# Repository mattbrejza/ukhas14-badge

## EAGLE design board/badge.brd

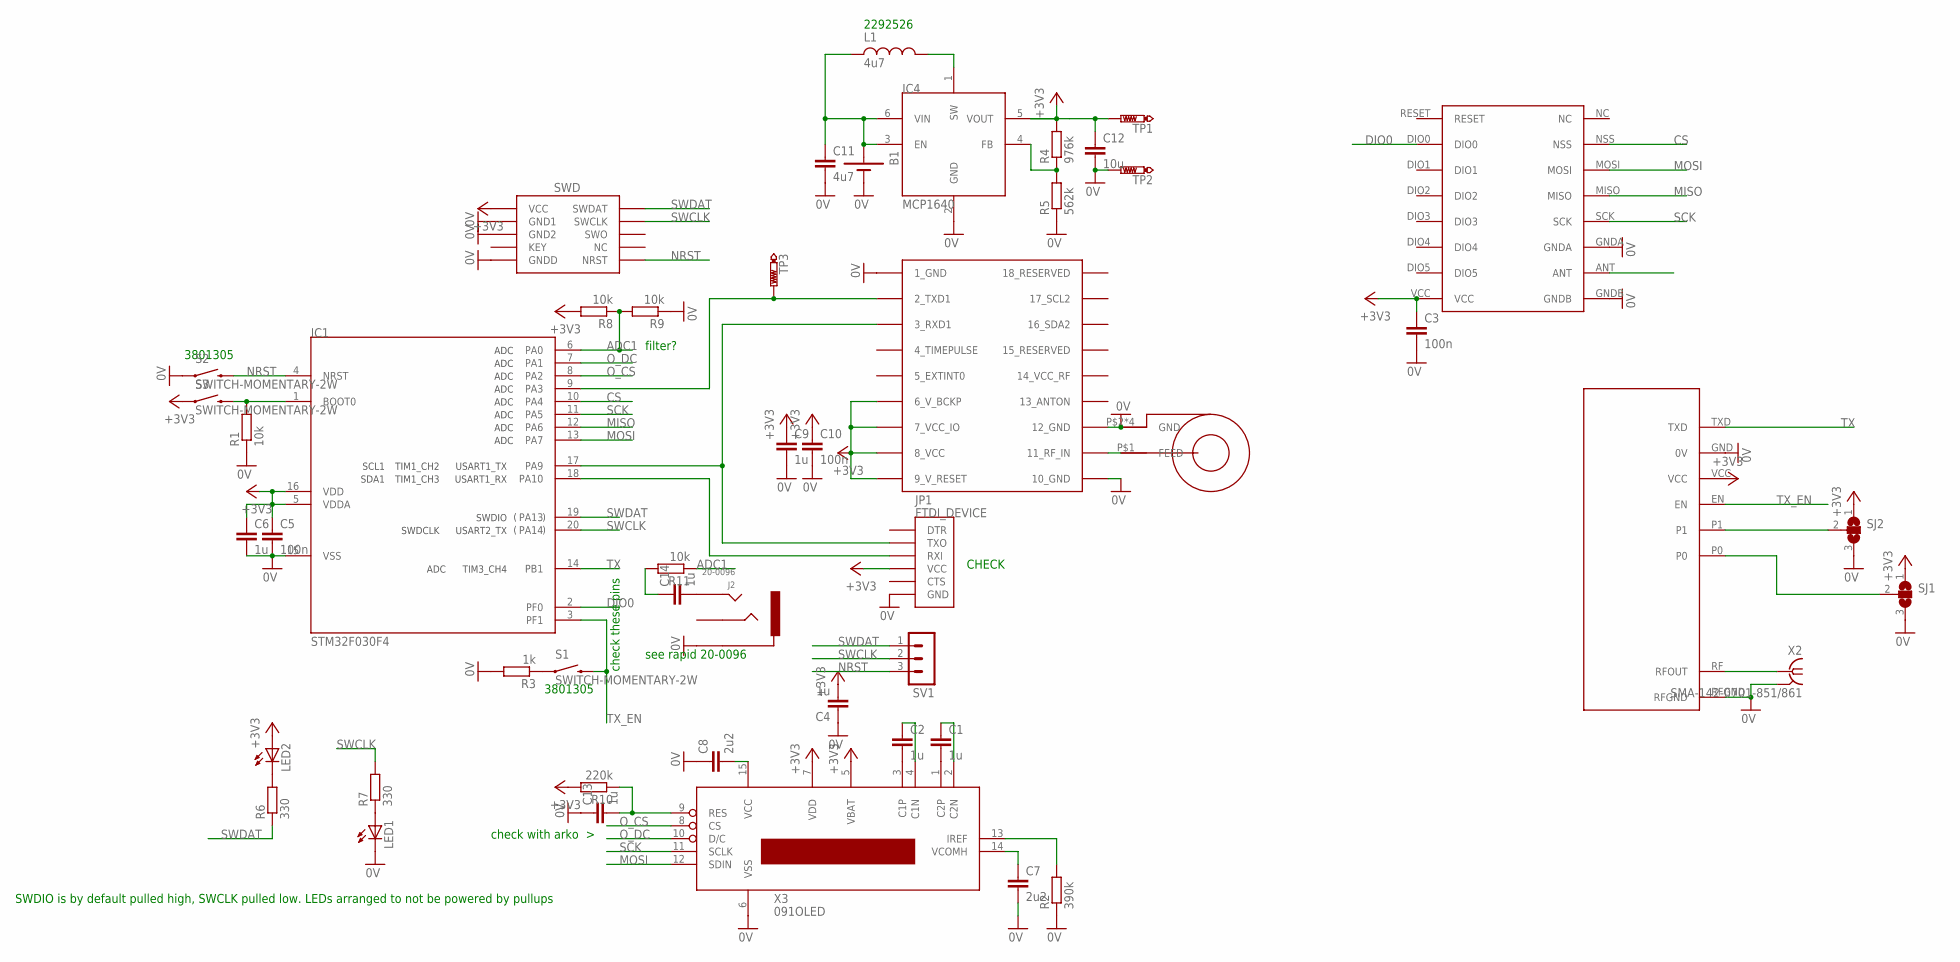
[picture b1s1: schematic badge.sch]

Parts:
B1: 1.5V-BATTERY-AAA-SMT-CLIPS; AAA-HOLDER-SMT-CLIPS
C1, C2, C4, C6, C9, C13, C14: 1u; C0603
C3, C5, C10: 100n; C0603
C7, C8: 2u2; C0603
C11: 4u7; C0805
C12: 10u; C0805
IC1: STM32F030F4; TSSOP20
IC2: UBLOX_MAX
IC3: RFM69HW; RFM
IC4: MCP1640; SOT23-6
J2: 20-0096; 3.5MMLOWPROFILE
J3: SWD_PTH_SHROUD
JP1: FTDI_DEVICE; FTDI_DEVICE_SIDE
L1: 4u7; INDUCTOR5X5
LED1, LED2: LED0603; LED-0603
R1, R8, R9, R11: 10k; R0603
R2: 390k; R0603
R3: 1k; R0603
R4: 976k; R0603
R5: 562k; R0603
R6, R7: 330; R0603
R10: 220k; R0603
S1, S2, S3: SWITCH-MOMENTARY-2W; TACTILE_WIDE
SJ1, SJ2: SJ2W; SJ_2
SV1: MA03-1
TP1, TP2, TP3: PTR1B2,54; B2,54
U$2: JDGA-REMQV-ANTENNA; JDGA-RIGID_COMBO_PAD
X1: RADIOMETRIX-MTX2
X2: SMA-142-0701-851/861; J502-ND-142-0701-851/861
X3: 091OLED; 0.91OLEDCON

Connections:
0V: B1.-1 (-), B1.-2 (-), C3.2, C4.1, C5.2, C6.2, C7.2, C8.1, C9.2, C10.2, C11.2, C12.2, C13.1, IC1.15 (VSS), IC2.1_GND, IC2.10_GND, IC2.12_GND, IC3.GNDA, IC3.GNDB, IC4.2 (GND), J2.2_1 (2), J2.2_2 (2), J3.3 (GND1), J3.5 (GND2), J3.9 (GNDD), JP1.P$6 (GND), LED1.C, R1.1, R2.1, R3.2, R5.1, R9.1, S2.A2 (1), SJ1.3, SJ2.3, TP2.TP, U$2.P$2 (GND), U$2.P$3 (GND), U$2.P$4 (GND), U$2.P$5 (GND), X1.GND (0V), X1.RFGND, X2.G@1 (2), X2.G@2 (2), X2.G@3 (2), X2.G@4 (2), X3.6 (VSS)
+3V3: C3.1, C4.2, C5.1, C6.1, C9.1, C10.1, C12.1, IC1.5 (VDDA), IC1.16 (VDD), IC2.6_V_BCKP, IC2.7_VCC_IO, IC2.8_VCC, IC2.9_V_RESET, IC3.VCC, IC4.5 (VOUT), J3.1 (VCC), JP1.P$4 (VCC), LED2.A, R4.2, R8.2, R10.2, S3.A2 (1), SJ1.1, SJ2.1, TP1.TP, X1.VCC, X3.5 (VBAT), X3.7 (VDD)
ADC1: IC1.6 (PA0), R8.1, R9.2, R11.1
CS: IC1.10 (PA4), IC3.NSS
DIO0: IC1.2 (PF0), IC3.DIO0
MISO: IC1.12 (PA6), IC3.MISO
MOSI: IC1.13 (PA7), IC3.MOSI, X3.12 (SDIN)
unnamed: IC2.11_RF_IN, U$2.P$1 (FEED)
unnamed: IC1.9 (PA3), IC2.2_TXD1, TP3.TP
unnamed: LED2.C, R6.2
unnamed: X1.RF (RFOUT), X2.1
unnamed: R2.2, X3.13 (IREF)
unnamed: IC1.1 (BOOT0), R1.2, S3.B2 (2)
unnamed: IC1.17 (PA9), IC2.3_RXD1, JP1.P$2 (TXO)
unnamed: IC1.18 (PA10), JP1.P$3 (RXI)
unnamed: C2.2, X3.3 (C1P)
unnamed: C1.2, X3.1 (C2P)
unnamed: C2.1, X3.4 (C1N)
unnamed: C1.1, X3.2 (C2N)
unnamed: IC4.4 (FB), R4.1, R5.2
unnamed: IC4.1 (SW), L1.P$2 (2)
unnamed: C7.1, X3.14 (VCOMH)
unnamed: LED1.A, R7.1
unnamed: SJ2.2, X1.P1
unnamed: R3.1, S1.A2 (1)
unnamed: SJ1.2, X1.P0
unnamed: C13.2, R10.1, X3.9 (RES)
unnamed: C14.2, J2.4_1 (4), J2.4_2 (4)
unnamed: C14.1, R11.2
NRST: IC1.4 (NRST), J3.10 (NRST), S2.B2 (2), SV1.3
O_CS: IC1.8 (PA2), X3.8 (CS)
O_DC: IC1.7 (PA1), X3.10 (D/C)
SCK: IC1.11 (PA5), IC3.SCK, X3.11 (SCLK)
SWCLK: IC1.20 (PA14), J3.4 (SWCLK), R7.2, SV1.2
SWDAT: IC1.19 (PA13), J3.2 (SWDAT), R6.1, SV1.1
TX: IC1.14 (PB1), X1.TXD
TX_EN: IC1.3 (PF1), S1.B2 (2), X1.EN
VCC: C8.2, X3.15 (VCC)
VIN: B1.+1 (+), B1.+2 (+), C11.1, IC4.3 (EN), IC4.6 (VIN), L1.P$1 (1)

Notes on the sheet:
see rapid 20-0096
check with arko >
check these pins
SWDIO is by default pulled high, SWCLK pulled low. LEDs arranged to not be powered by pullups
filter?
2292526
3801305
CHECK

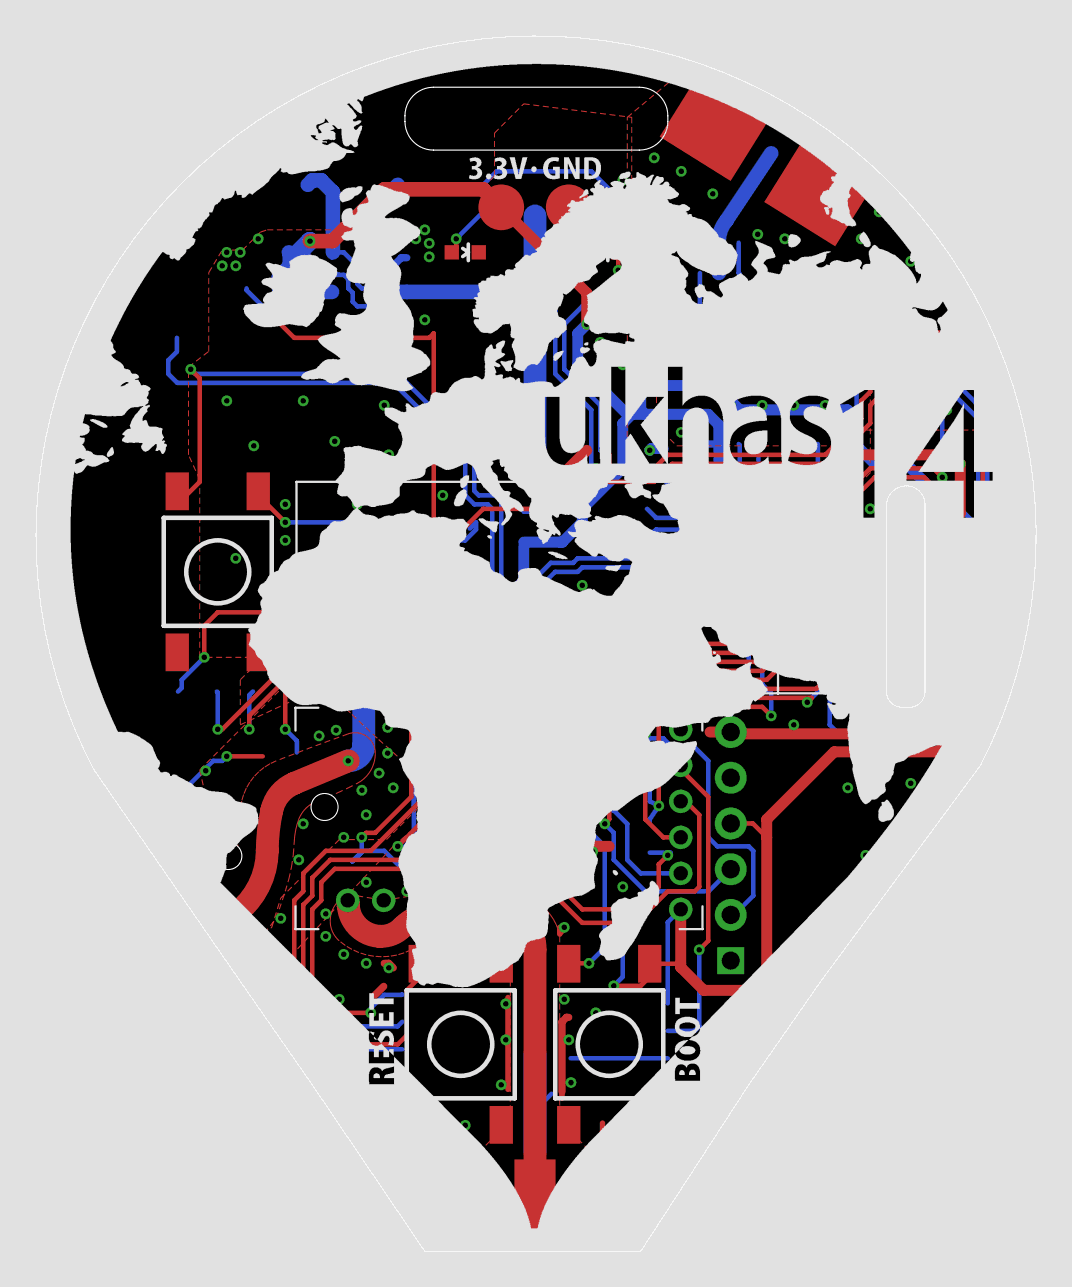
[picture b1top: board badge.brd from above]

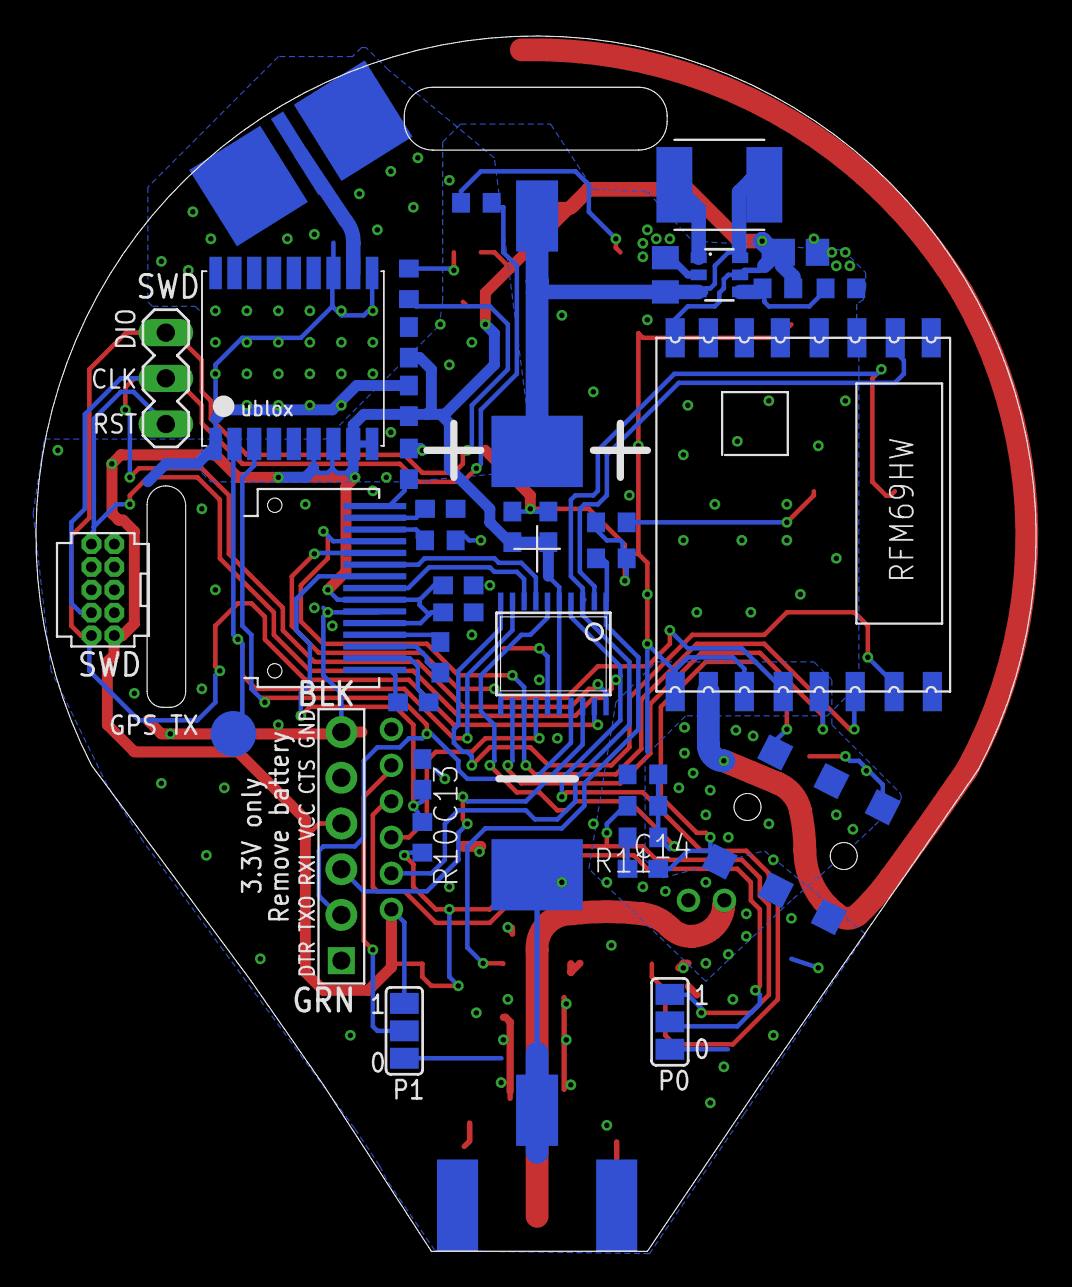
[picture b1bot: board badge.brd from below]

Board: 2 copper layers, 55.6 x 67.5 mm, 50 parts (40 on the bottom side), 39 nets.

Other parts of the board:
U$1: 0.91OLEDPANEL

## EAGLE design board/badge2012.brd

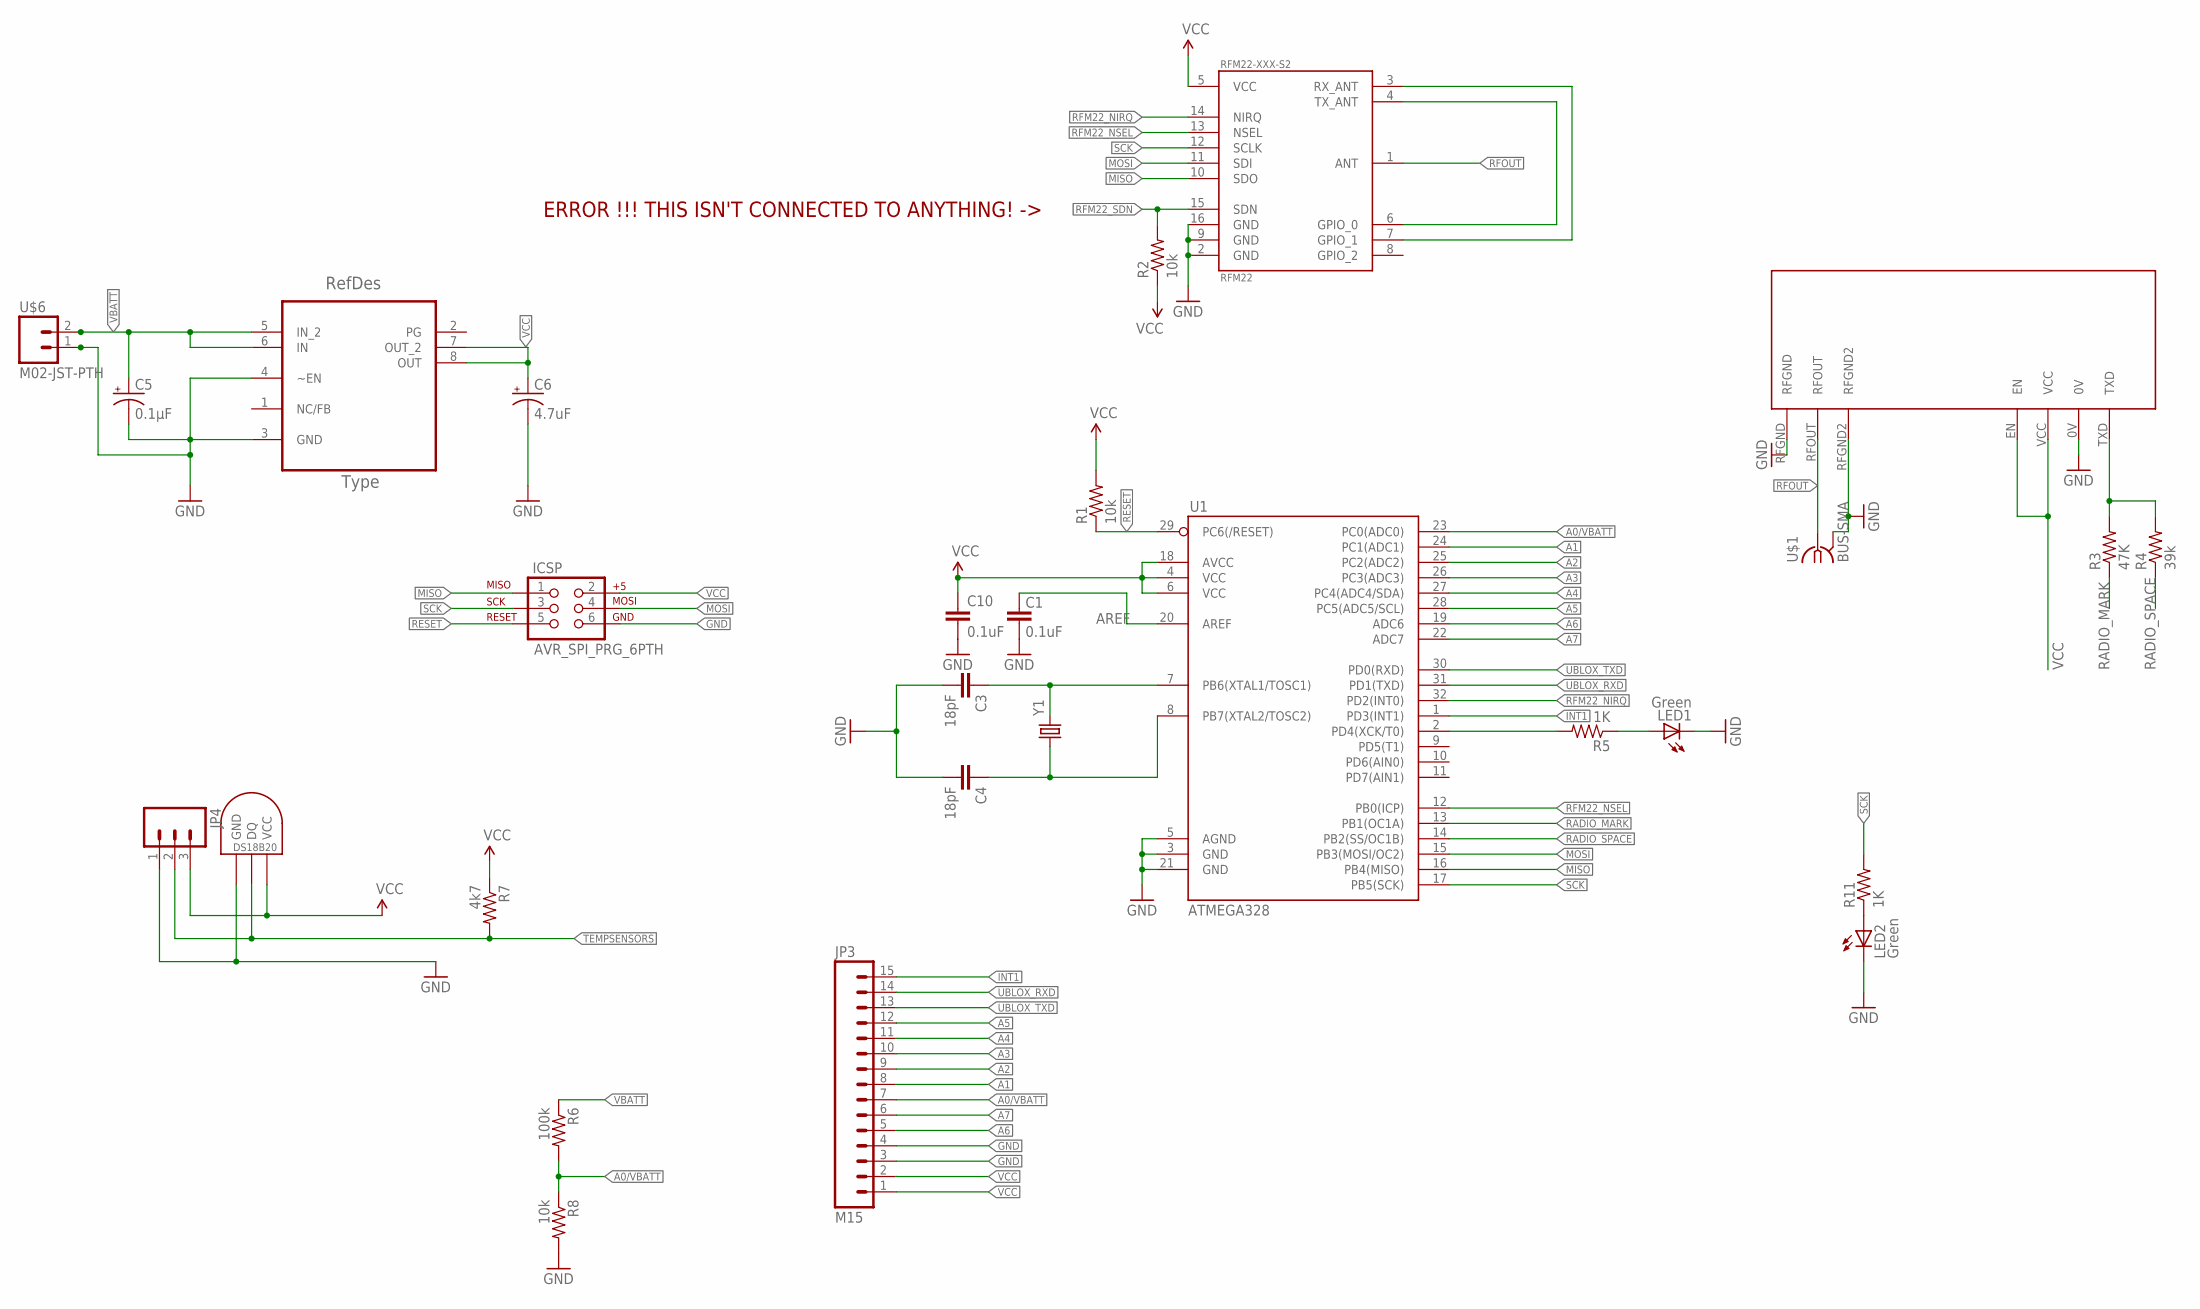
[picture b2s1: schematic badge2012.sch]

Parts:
C1, C10: 0.1uF; 0603-CAP
C3, C4: 18pF; 0603-CAP
C5: 0.1µF; EIA3216-KIT
C6: 4.7uF; EIA3216-KIT
ICSP: AVR_SPI_PRG_6PTH; 2X3
JP3: M15; 1X15
JP4: M03PTH; 1X03
LED1, LED2: Green; LED-0603
NTX2TEMP: DS1821; DS18B20_SOIC
R1, R2, R8: 10k; 0603-RES
R3: 47K; 0603-RES
R4: 39k; 0603-RES
R5, R11: 1K; 0603-RES
R6: 100k; 0603-RES
R7: 4k7; 0603-RES
RFM22-XXX-S2: RFM22; RFM22-XXX-S2
U1: ATMEGA328; TQFP32-08
U2: TPS76633D; SOIC127P600X175-8N
U$1: BUS-SMA
U$4: NTX2
U$6: M02-JST-PTH
Y1: CRYSTALSMD; HC49UP

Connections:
A0/VBATT: JP3.7, R6.2, R8.1, U1.23 (PC0(ADC0))
A1: JP3.8, U1.24 (PC1(ADC1))
A2: JP3.9, U1.25 (PC2(ADC2))
A3: JP3.10, U1.26 (PC3(ADC3))
A4: JP3.11, U1.27 (PC4(ADC4/SDA))
A5: JP3.12, U1.28 (PC5(ADC5/SCL))
A6: JP3.5, U1.19 (ADC6)
A7: JP3.6, U1.22 (ADC7)
AREF: C1.2, U1.20 (AREF)
GND: C1.1, C3.2, C4.2, C5.C (-), C6.C (-), C10.2, ICSP.6, JP3.3, JP3.4, JP4.1, LED1.C, LED2.C, NTX2TEMP.GND, R8.2, RFM22-XXX-S2.2 (GND), RFM22-XXX-S2.9 (GND), RFM22-XXX-S2.16 (GND), U1.3 (GND), U1.5 (AGND), U1.21 (GND), U2.3 (GND), U2.4 (~EN), U$1.2 (GND), U$1.3 (GND), U$1.4 (GND), U$1.5 (GND), U$4.0V, U$4.RFGND, U$4.RFGND2, U$6.1
INT1: JP3.15, U1.1 (PD3(INT1))
MISO: ICSP.1, RFM22-XXX-S2.10 (SDO), U1.16 (PB4(MISO))
MOSI: ICSP.4, RFM22-XXX-S2.11 (SDI), U1.15 (PB3(MOSI/OC2))
unnamed: R5.2, U1.2 (PD4(XCK/T0))
unnamed: R3.2, R4.2, U$4.TXD
unnamed: LED1.A, R5.1
unnamed: RFM22-XXX-S2.3 (RX_ANT), RFM22-XXX-S2.7 (GPIO_1)
unnamed: RFM22-XXX-S2.4 (TX_ANT), RFM22-XXX-S2.6 (GPIO_0)
unnamed: LED2.A, R11.1
unnamed: C3.1, U1.7 (PB6(XTAL1/TOSC1)), Y1.2
unnamed: C4.1, U1.8 (PB7(XTAL2/TOSC2)), Y1.1
RADIO_MARK: R3.1, U1.13 (PB1(OC1A))
RADIO_SPACE: R4.1, U1.14 (PB2(SS/OC1B))
RESET: ICSP.5, R1.1, U1.29 (PC6(/RESET))
RFM22_NIRQ: RFM22-XXX-S2.14 (NIRQ), U1.32 (PD2(INT0))
RFM22_NSEL: RFM22-XXX-S2.13 (NSEL), U1.12 (PB0(ICP))
RFM22_SDN: R2.2, RFM22-XXX-S2.15 (SDN)
RFOUT: RFM22-XXX-S2.1 (ANT), U$1.1, U$4.RFOUT
SCK: ICSP.3, R11.2, RFM22-XXX-S2.12 (SCLK), U1.17 (PB5(SCK))
TEMPSENSORS: JP4.2, NTX2TEMP.DQ, R7.2
UBLOX_RXD: JP3.14, U1.31 (PD1(TXD))
UBLOX_TXD: JP3.13, U1.30 (PD0(RXD))
VBATT: C5.A (+), R6.1, U2.5 (IN_2), U2.6 (IN), U$6.2
VCC: C6.A (+), C10.1, ICSP.2, JP3.1, JP3.2, JP4.3, NTX2TEMP.VCC, R1.2, R2.1, R7.1, RFM22-XXX-S2.5 (VCC), U1.4 (VCC), U1.6 (VCC), U1.18 (AVCC), U2.7 (OUT_2), U2.8 (OUT), U$4.EN, U$4.VCC

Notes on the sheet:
ERROR !!! THIS ISN'T CONNECTED TO ANYTHING! ->

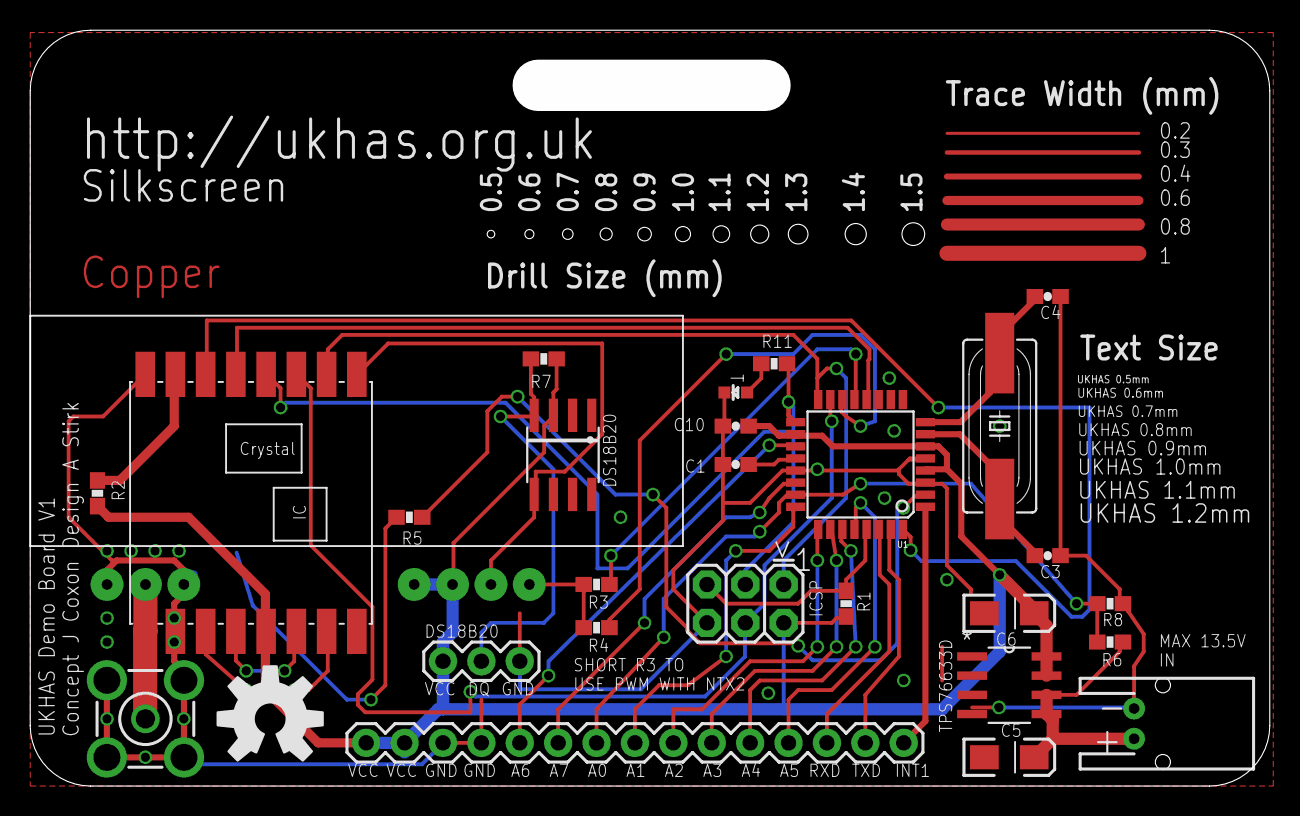
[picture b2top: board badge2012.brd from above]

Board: 2 copper layers, 82.0 x 50.0 mm, 29 parts (1 on the bottom side), 34 nets.

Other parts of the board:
U$2: OSHW-LOGO-L

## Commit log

2014-05-20 schematic mostly done
2014-05-21 got bored, moved parts around
2014-05-21 added mtx2 jumpers
2014-05-21 Outline Placeholder
    And old boards for reference.
2014-05-21 initial route
2014-05-22 routing almost done
2014-05-24 almost done
2014-05-24 drc fixes
2014-05-24 adding part numbers
2014-05-25 Tidy up
    Replaced octagonal vias with round ones
    Replaced 0.381mm vias with 0.3mm
    Fixed 3 airwires
    Amended 20 Dimension to width 0
2014-05-25 adding DC bias resistors
2014-05-25 Tied Reset pin on GPS to VCC
2014-05-26 Amended milling layer
    Made them dimension layer instead. Confuses the fab by 87.2% less.
2014-06-17 First go at locm3 firmware
2014-06-17 First stab at LCD init, completely untested
2014-06-18 LCD powers on successfully, just need to tidy up command definitions a bit
2014-06-18 Defines mostly done for the LCD, code is a bit nicer
2014-06-18 Test 9 bit SPI for 3 wire SPI control of the LCD
2014-06-25 Updated pin defs and startup routing for bodged rev.A board
2014-06-26 started rev2
2014-06-26 rev2 almost done
2014-06-28 switching tx/rx on ftdi
2014-06-28 screen can display text
2014-06-28 some small changes
2014-06-29 minor changes (might have fixed ftdi in this one)
2014-06-30 pwm works
2014-07-02 Added silkscreen graphics files
2014-07-02 Top silkscreen graphic added.
2014-07-15 Update libopencm3.
2014-07-15 Change BMP_PORT for linux.
2014-07-15 Add gedit backup files to gitignore.
2014-07-15 Change name to Phil.
2014-07-16 Add WIP rfm69 lib.
2014-07-16 Add source files locally for now.
2014-07-16 Moved RFM globals into C file and declared static. Fixes build failure caused by redeclaration of globals
2014-08-09 adding rtty demod stuff
2014-08-09 added sync stuff
2014-08-09 needs adc stuff now
2014-08-12 dma is being shit
2014-08-13 still not working
2014-08-13 fixing mega derp
2014-08-13 mostly works, bit sync aint great
2014-08-13 fixed char sync
2014-08-15 set oscillator to max, tidied up
2014-09-05 updating type names
2014-09-05 cleaning up

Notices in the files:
parts and their libraries:
SparkFun-Connectors: Licensing: CC v3.0 Share-Alike You are welcome to use this library for commercial purposes.
